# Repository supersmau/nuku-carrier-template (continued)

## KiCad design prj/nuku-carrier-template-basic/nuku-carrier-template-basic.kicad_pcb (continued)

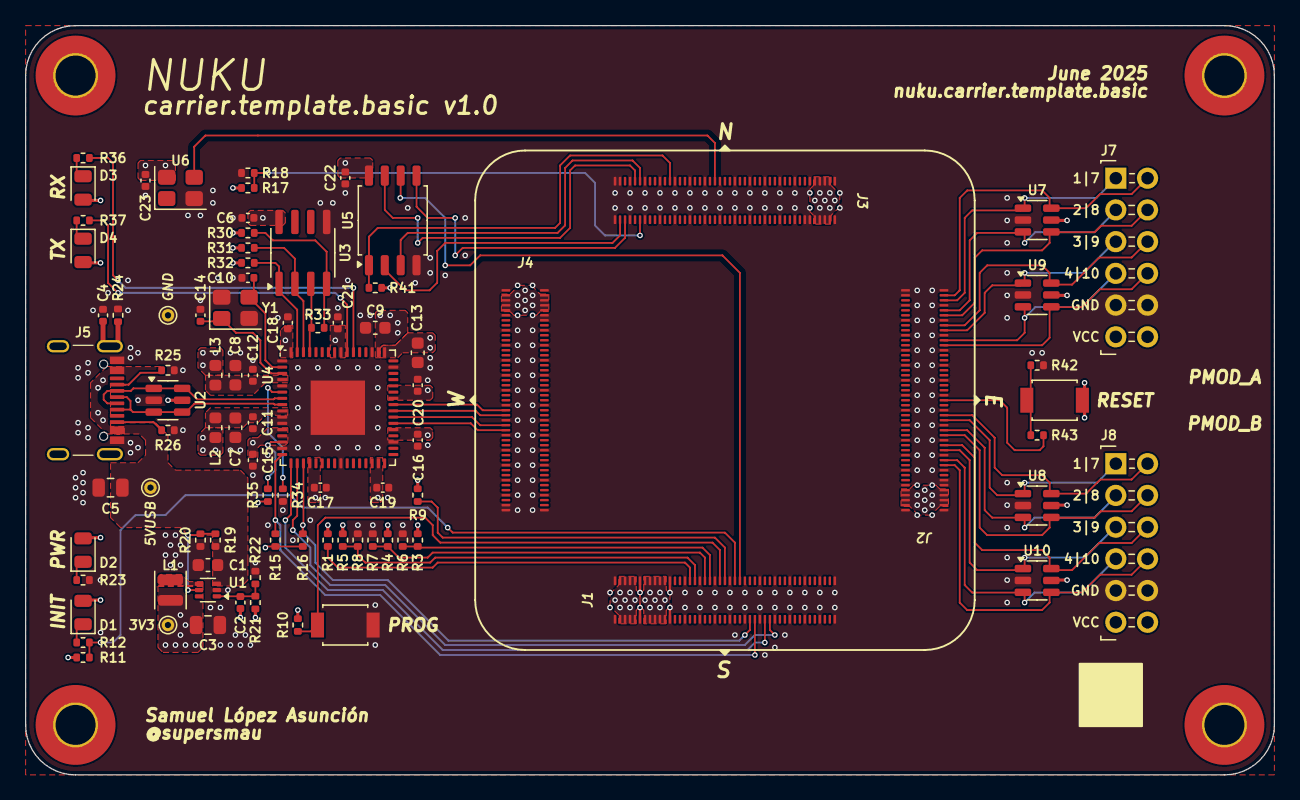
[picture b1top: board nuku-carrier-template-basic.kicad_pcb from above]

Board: 4 copper layers, 100.0 x 60.0 mm, 87 parts (0 on the bottom side), 69 nets.

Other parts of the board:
3V3, 5VUSB: TestPoint_THTPad_D1.0mm_Drill0.5mm
GND: TestPoint_THTPad_D1.0mm_Drill0.5mm

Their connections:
+3V3: 3V3.1; also elsewhere on the board
+5V: 5VUSB.1; also elsewhere on the board
GND: GND.1; also elsewhere on the board

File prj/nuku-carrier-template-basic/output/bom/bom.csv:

"Reference","Value","Footprint","Qty","DNP","LCSC"
"C1,C7,C8,C9,C13","4u7","Capacitor_SMD:C_0603_1608Metric","5","","C19666"
"C2,C10,C14","33p","Capacitor_SMD:C_0402_1005Metric","3","","C1562"
"C3,C5","47u","Capacitor_SMD:C_0805_2012Metric","2","","C16780"
"C4,C6,C11,C12,C15,C16,C17,C18,C19,C20,C21,C22,C23","470n","Capacitor_SMD:C_0402_1005Metric","13","","C47339"
"D1,D2,D3,D4","INIT,PWR,RX,TX","LED_SMD:LED_0805_2012Metric","4","","C2297"
"J1,J2,J3,J4","DF40HC(4.0)-90DS-0.4V","nuku:DF40HC(4.0)-90DS-0.4V","4","","C597947"
"J5","USB_C_Receptacle_USB2.0_16P","nuku:TYPE-C16PIN","1","","C393939"
"J7,J8","PMOD_A,PMOD_B","nuku:PMOD_PinSocket_2x06_P2.54mm_Horizontal","2","","C2936003"
"L1","1u","Inductor_SMD:L_Changjiang_FNR252010S","1","","C5832356"
"L2,L3","600","Inductor_SMD:L_0603_1608Metric","2","","C1002"
"R1,R38","0","Resistor_SMD:R_0402_1005Metric","2","","C17168"
"R5,R6,R7,R12,R17,R23,R35,R36,R37","1k","Resistor_SMD:R_0402_1005Metric","9","","C11702"
"R9","330","Resistor_SMD:R_0402_1005Metric","1","","C25104"
"R10,R11,R41,R42,R43","4k7","Resistor_SMD:R_0402_1005Metric","5","","C25900"
"R15,R16,R30,R31,R32","10k","Resistor_SMD:R_0402_1005Metric","5","","C25744"
"R19,R21","100k","Resistor_SMD:R_0402_1005Metric","2","","C25741"
"R20","200k","Resistor_SMD:R_0402_1005Metric","1","","C25764"
"R22","22k","Resistor_SMD:R_0402_1005Metric","1","","C25768"
"R24","1M","Resistor_SMD:R_0402_1005Metric","1","","C26083"
"R25,R26","5k1","Resistor_SMD:R_0402_1005Metric","2","","C25905"
"R33","2k2","Resistor_SMD:R_0402_1005Metric","1","","C25879"
"R34","12k","Resistor_SMD:R_0402_1005Metric","1","","C25752"
"SW1,SW2","PROG,RESET","nuku:TS-1088-AR02016","2","","C720477"
"U1","AP61302","Package_TO_SOT_SMD:SOT-563","1","","C3193204"
"U2,U7,U8,U9,U10","SRV05-4","Package_TO_SOT_SMD:SOT-23-6","5","","C7420376"
"U3","M93C56-WDW6TP","Package_SO:TSSOP-8_4.4x3mm_P0.65mm","1","","C2061074"
"U4","FT2232HQ","Package_DFN_QFN:QFN-64-1EP_9x9mm_P0.5mm_EP4.35x4.35mm","1","","C193662"
"U5","IS25LP064A","Package_SO:SOIC-8_5.3x5.3mm_P1.27mm","1","","C2841348"
"U6","OT3225100MJBA4SL","Crystal:Crystal_SMD_3225-4Pin_3.2x2.5mm","1","","C4353707"
"Y1","12 MHz","Crystal:Crystal_SMD_3225-4Pin_3.2x2.5mm","1","","C9002"

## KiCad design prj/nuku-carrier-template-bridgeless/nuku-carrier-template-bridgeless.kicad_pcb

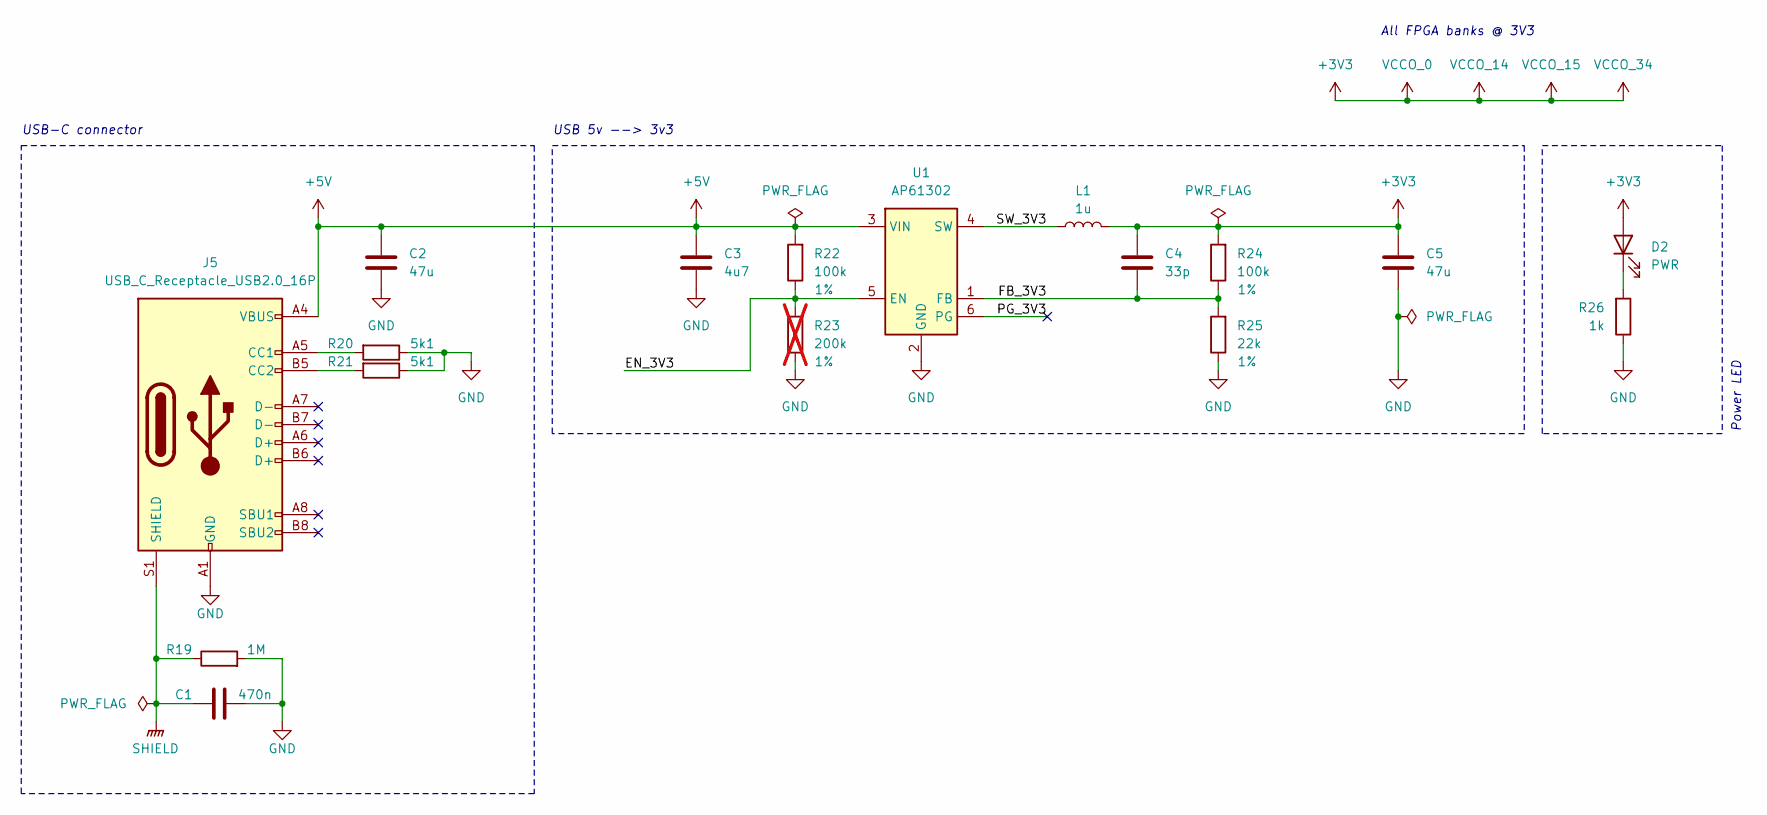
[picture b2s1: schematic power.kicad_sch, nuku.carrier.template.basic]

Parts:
C1: 470n; C_0402_1005Metric; LCSC C47339
C2, C5: 47u; C_0805_2012Metric; LCSC C16780
C3: 4u7; C_0603_1608Metric; LCSC C19666
C4: 33p; C_0402_1005Metric; LCSC C1562
D2: PWR; LED_0805_2012Metric; LCSC C2297
J5: USB_C_Receptacle_USB2.0_16P; TYPE-C16PIN; LCSC C393939
L1: 1u; L_Changjiang_FNR252010S; Mfr. Part FTC252010S1R0MBCA; LCSC C5832356
R19: 1M; R_0402_1005Metric; LCSC C26083
R20, R21: 5k1; R_0402_1005Metric; LCSC C25905
R22, R24: 100k; R_0402_1005Metric; Tolerance 1%; LCSC C25741
R23: 200k; R_0402_1005Metric; Tolerance 1%; LCSC C25764; not fitted
R25: 22k; R_0402_1005Metric; Tolerance 1%; LCSC C25768
R26: 1k; R_0402_1005Metric; LCSC C11702
U1: AP61302; SOT-563; LCSC C3193204

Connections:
+3V3: C4.1, C5.1, D2.2 (A), L1.2, R24.2; also elsewhere on the board
+5V: C2.1, C3.1, J5.A4 (VBUS), J5.A9 (VBUS), J5.B4 (VBUS), J5.B9 (VBUS), R22.2, U1.3 (VIN); also elsewhere on the board
/power/EN_3V3: R22.1, R23.2, U1.5 (EN)
/power/FB_3V3: C4.2, R24.1, R25.2, U1.1 (FB)
/power/PG_3V3: U1.6 (PG)
/power/SW_3V3: L1.1, U1.4 (SW)
GND: C1.1, C2.2, C3.2, C5.2, J5.A1 (GND), J5.A12 (GND), J5.B1 (GND), J5.B12 (GND), R19.2, R20.1, R21.1, R23.1, R25.1, R26.1, U1.2 (GND); also elsewhere on the board
unnamed: D2.1 (K), R26.2
unnamed: J5.A5 (CC1), R20.2
unnamed: J5.B5 (CC2), R21.2
SHIELD: C1.2, J5.S1 (SHIELD), R19.1

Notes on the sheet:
USB-C connector
All FPGA banks @ 3V3
USB 5v --> 3v3
Power LED

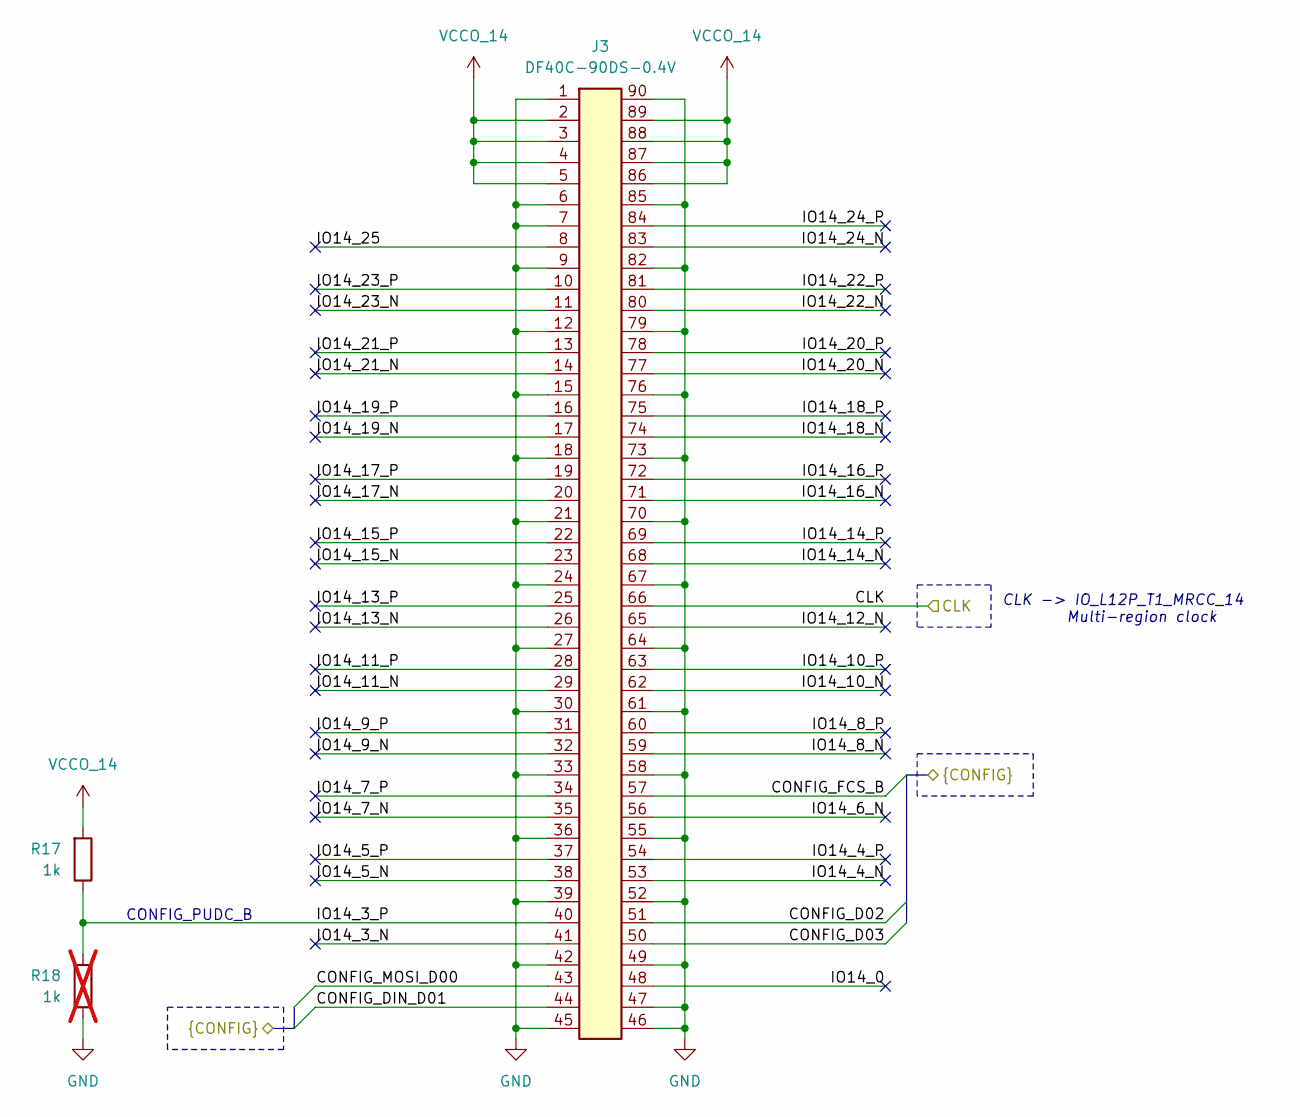
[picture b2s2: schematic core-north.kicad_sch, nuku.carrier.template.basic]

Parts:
J3: DF40C-90DS-0.4V; LCSC C2911197
R17: 1k; R_0402_1005Metric; LCSC C11702
R18: 1k; R_0402_1005Metric; LCSC C11702; not fitted

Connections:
+3V3: J3.2, J3.3, J3.4, J3.5, J3.86, J3.87, J3.88, J3.89, R17.2; also elsewhere on the board
/config/CLK: J3.66; also elsewhere on the board
/config/CONFIG_D02: J3.51; also elsewhere on the board
/config/CONFIG_D03: J3.50; also elsewhere on the board
/config/CONFIG_DIN_D01: J3.44; also elsewhere on the board
/config/CONFIG_FCS_B: J3.57; also elsewhere on the board
/config/CONFIG_MOSI_D00: J3.43; also elsewhere on the board
/core-north-14/IO14_0: J3.48
/core-north-14/IO14_3_N: J3.41
/core-north-14/IO14_3_P: J3.40, R17.1, R18.2
/core-north-14/IO14_4_N: J3.53
/core-north-14/IO14_4_P: J3.54
/core-north-14/IO14_5_N: J3.38
/core-north-14/IO14_5_P: J3.37
/core-north-14/IO14_6_N: J3.56
/core-north-14/IO14_7_N: J3.35
/core-north-14/IO14_7_P: J3.34
/core-north-14/IO14_8_N: J3.59
/core-north-14/IO14_8_P: J3.60
/core-north-14/IO14_9_N: J3.32
/core-north-14/IO14_9_P: J3.31
/core-north-14/IO14_10_N: J3.62
/core-north-14/IO14_10_P: J3.63
/core-north-14/IO14_11_N: J3.29
/core-north-14/IO14_11_P: J3.28
/core-north-14/IO14_12_N: J3.65
/core-north-14/IO14_13_N: J3.26
/core-north-14/IO14_13_P: J3.25
/core-north-14/IO14_14_N: J3.68
/core-north-14/IO14_14_P: J3.69
/core-north-14/IO14_15_N: J3.23
/core-north-14/IO14_15_P: J3.22
/core-north-14/IO14_16_N: J3.71
/core-north-14/IO14_16_P: J3.72
/core-north-14/IO14_17_N: J3.20
/core-north-14/IO14_17_P: J3.19
/core-north-14/IO14_18_N: J3.74
/core-north-14/IO14_18_P: J3.75
/core-north-14/IO14_19_N: J3.17
/core-north-14/IO14_19_P: J3.16
/core-north-14/IO14_20_N: J3.77
/core-north-14/IO14_20_P: J3.78
/core-north-14/IO14_21_N: J3.14
/core-north-14/IO14_21_P: J3.13
/core-north-14/IO14_22_N: J3.80
/core-north-14/IO14_22_P: J3.81
/core-north-14/IO14_23_N: J3.11
/core-north-14/IO14_23_P: J3.10
/core-north-14/IO14_24_N: J3.83
/core-north-14/IO14_24_P: J3.84
/core-north-14/IO14_25: J3.8
GND: J3.1, J3.6, J3.7, J3.9, J3.12, J3.15, J3.18, J3.21, J3.24, J3.27, J3.30, J3.33, J3.36, J3.39, J3.42, J3.45, J3.46, J3.47, J3.49, J3.52, J3.55, J3.58, J3.61, J3.64, J3.67, J3.70, J3.73, J3.76, J3.79, J3.82, J3.85, J3.90, R18.1; also elsewhere on the board

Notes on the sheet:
CONFIG_PUDC_B
CLK -> IO_L12P_T1_MRCC_14 Multi-region clock

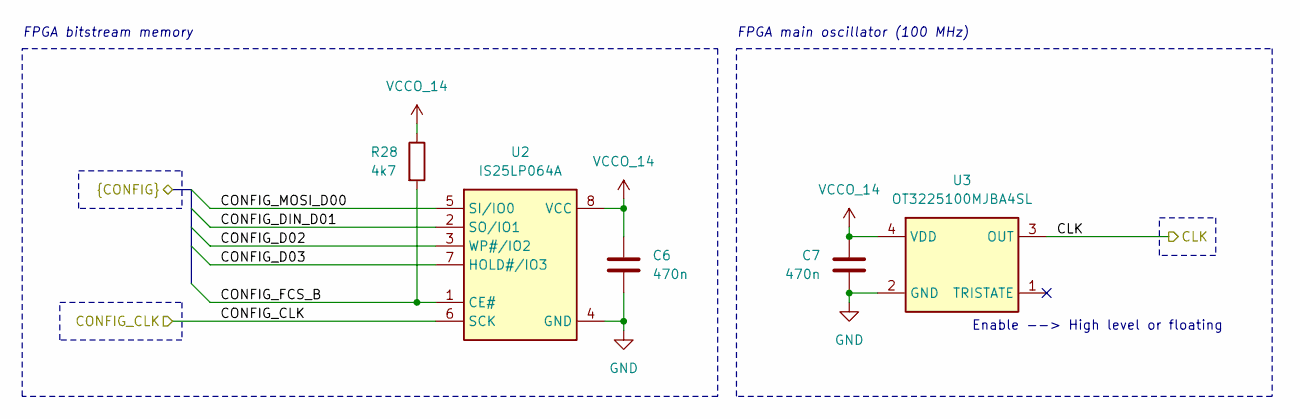
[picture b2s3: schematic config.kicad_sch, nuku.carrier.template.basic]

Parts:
C6, C7: 470n; C_0402_1005Metric; LCSC C47339
R28: 4k7; R_0402_1005Metric; LCSC C25900
U2: IS25LP064A; SOIC-8_5.3x5.3mm_P1.27mm; LCSC C2841348
U3: OT3225100MJBA4SL; Crystal_SMD_3225-4Pin_3.2x2.5mm; LCSC C4353707

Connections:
+3V3: C6.1, C7.1, R28.1, U2.8 (VCC), U3.4 (VDD); also elsewhere on the board
/config/CLK: U3.3 (OUT); also elsewhere on the board
/config/CONFIG_CLK: U2.6 (SCK); also elsewhere on the board
/config/CONFIG_D02: U2.3 (WP#/IO2); also elsewhere on the board
/config/CONFIG_D03: U2.7 (HOLD#/IO3); also elsewhere on the board
/config/CONFIG_DIN_D01: U2.2 (SO/IO1); also elsewhere on the board
/config/CONFIG_FCS_B: R28.2, U2.1 (CE#); also elsewhere on the board
/config/CONFIG_MOSI_D00: U2.5 (SI/IO0); also elsewhere on the board
GND: C6.2, C7.2, U2.4 (GND), U3.2 (GND); also elsewhere on the board

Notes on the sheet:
Enable --> High level or floating
FPGA main oscillator (100 MHz)
FPGA bitstream memory

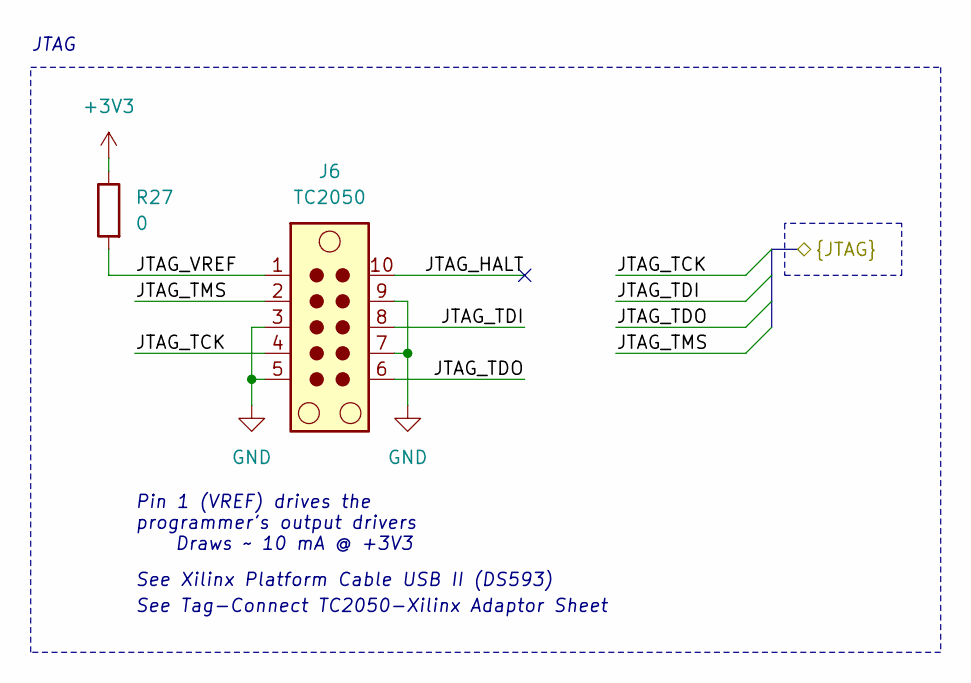
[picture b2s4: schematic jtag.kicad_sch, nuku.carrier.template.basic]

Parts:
J6: TC2050; Tag-Connect_TC2050-IDC-FP_2x05_P1.27mm_Vertical
R27: 0; R_0402_1005Metric; LCSC C17168

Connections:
+3V3: R27.1; also elsewhere on the board
/core-south-0/JTAG_TCK: J6.4; also elsewhere on the board
/core-south-0/JTAG_TDI: J6.8; also elsewhere on the board
/core-south-0/JTAG_TDO: J6.6; also elsewhere on the board
/core-south-0/JTAG_TMS: J6.2; also elsewhere on the board
/jtag/JTAG_HALT: J6.10
/jtag/JTAG_VREF: J6.1, R27.2
GND: J6.3, J6.5, J6.7, J6.9; also elsewhere on the board

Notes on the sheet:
Pin 1 (VREF) drives the programmer's output drivers Draws ~ 10 mA @ +3V3
See Tag-Connect TC2050-Xilinx Adaptor Sheet
See Xilinx Platform Cable USB II (DS593)
JTAG

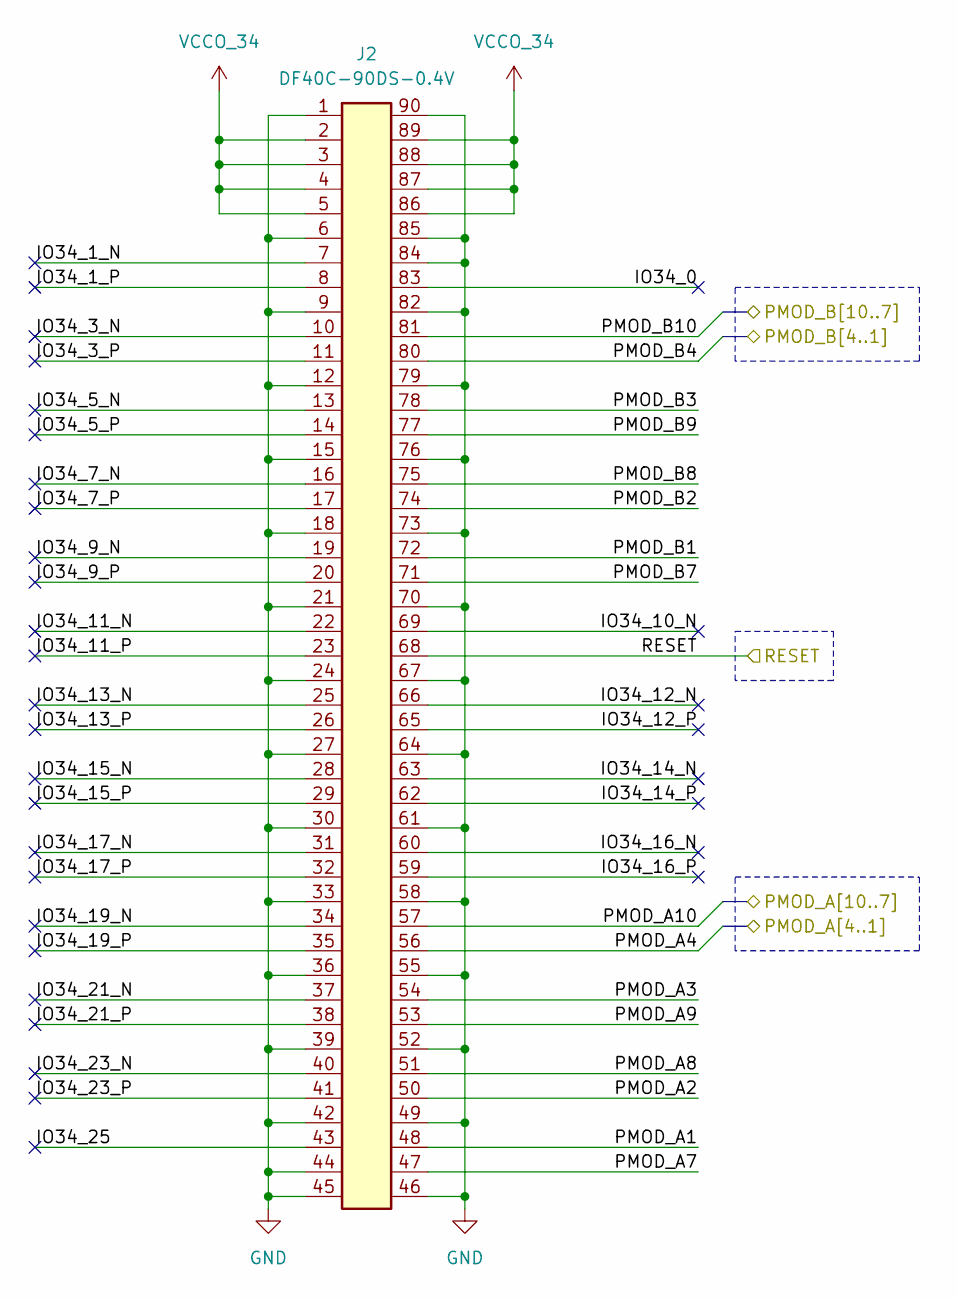
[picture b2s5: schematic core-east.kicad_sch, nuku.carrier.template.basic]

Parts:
J2: DF40C-90DS-0.4V; LCSC C2911197

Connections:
+3V3: J2.2, J2.3, J2.4, J2.5, J2.86, J2.87, J2.88, J2.89; also elsewhere on the board
/core-east-34/IO34_0: J2.83
/core-east-34/IO34_1_N: J2.7
/core-east-34/IO34_1_P: J2.8
/core-east-34/IO34_3_N: J2.10
/core-east-34/IO34_3_P: J2.11
/core-east-34/IO34_5_N: J2.13
/core-east-34/IO34_5_P: J2.14
/core-east-34/IO34_7_N: J2.16
/core-east-34/IO34_7_P: J2.17
/core-east-34/IO34_9_N: J2.19
/core-east-34/IO34_9_P: J2.20
/core-east-34/IO34_10_N: J2.69
/core-east-34/IO34_11_N: J2.22
/core-east-34/IO34_11_P: J2.23
/core-east-34/IO34_12_N: J2.66
/core-east-34/IO34_12_P: J2.65
/core-east-34/IO34_13_N: J2.25
/core-east-34/IO34_13_P: J2.26
/core-east-34/IO34_14_N: J2.63
/core-east-34/IO34_14_P: J2.62
/core-east-34/IO34_15_N: J2.28
/core-east-34/IO34_15_P: J2.29
/core-east-34/IO34_16_N: J2.60
/core-east-34/IO34_16_P: J2.59
/core-east-34/IO34_17_N: J2.31
/core-east-34/IO34_17_P: J2.32
/core-east-34/IO34_19_N: J2.34
/core-east-34/IO34_19_P: J2.35
/core-east-34/IO34_21_N: J2.37
/core-east-34/IO34_21_P: J2.38
/core-east-34/IO34_23_N: J2.40
/core-east-34/IO34_23_P: J2.41
/core-east-34/IO34_25: J2.43
/core-east-34/PMOD_A1: J2.48; also elsewhere on the board
/core-east-34/PMOD_A2: J2.50; also elsewhere on the board
/core-east-34/PMOD_A3: J2.54; also elsewhere on the board
/core-east-34/PMOD_A4: J2.56; also elsewhere on the board
/core-east-34/PMOD_A7: J2.47; also elsewhere on the board
/core-east-34/PMOD_A8: J2.51; also elsewhere on the board
/core-east-34/PMOD_A9: J2.53; also elsewhere on the board
/core-east-34/PMOD_A10: J2.57; also elsewhere on the board
/core-east-34/PMOD_B1: J2.72; also elsewhere on the board
/core-east-34/PMOD_B2: J2.74; also elsewhere on the board
/core-east-34/PMOD_B3: J2.78; also elsewhere on the board
/core-east-34/PMOD_B4: J2.80; also elsewhere on the board
/core-east-34/PMOD_B7: J2.71; also elsewhere on the board
/core-east-34/PMOD_B8: J2.75; also elsewhere on the board
/core-east-34/PMOD_B9: J2.77; also elsewhere on the board
/core-east-34/PMOD_B10: J2.81; also elsewhere on the board
/core-east-34/RESET: J2.68; also elsewhere on the board
GND: J2.1, J2.6, J2.9, J2.12, J2.15, J2.18, J2.21, J2.24, J2.27, J2.30, J2.33, J2.36, J2.39, J2.42, J2.44, J2.45, J2.46, J2.49, J2.52, J2.55, J2.58, J2.61, J2.64, J2.67, J2.70, J2.73, J2.76, J2.79, J2.82, J2.84, J2.85, J2.90; also elsewhere on the board

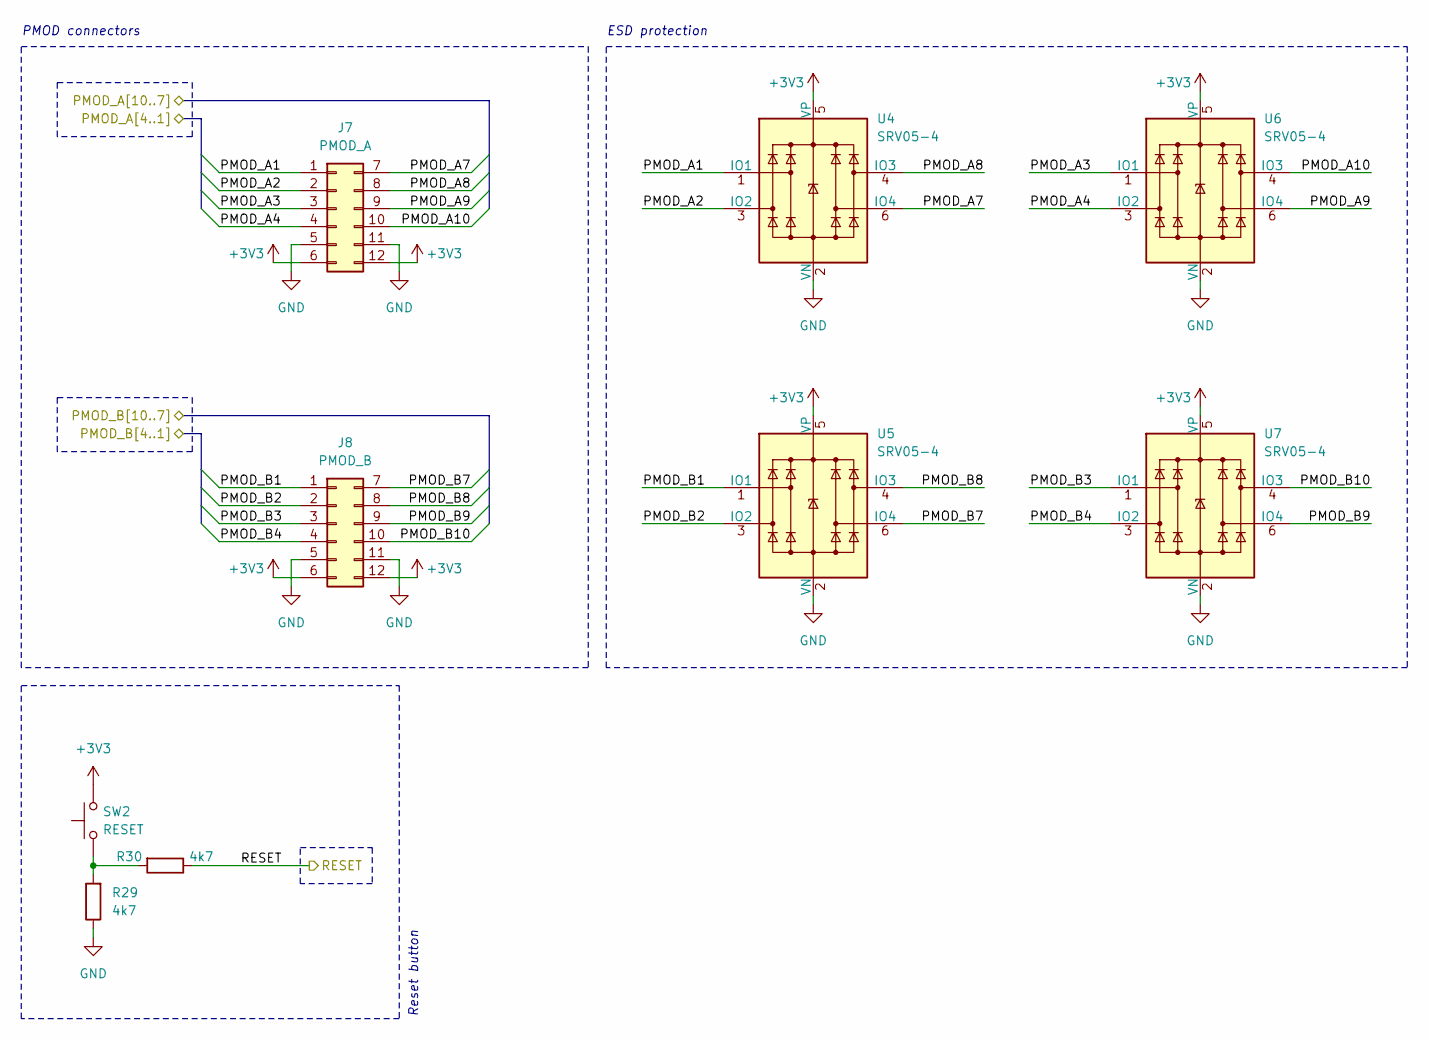
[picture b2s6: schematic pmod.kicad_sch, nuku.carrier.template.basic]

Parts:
J7: PMOD_A; PMOD_PinSocket_2x06_P2.54mm_Horizontal; LCSC C2936003
J8: PMOD_B; PMOD_PinSocket_2x06_P2.54mm_Horizontal; LCSC C2936003
R29, R30: 4k7; R_0402_1005Metric; LCSC C25900
SW2: RESET; TS-1088-AR02016; LCSC C720477
U4, U5, U6, U7: SRV05-4; SOT-23-6; LCSC C7420376

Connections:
+3V3: J7.6, J7.12, J8.6, J8.12, SW2.2, U4.5 (VP), U5.5 (VP), U6.5 (VP), U7.5 (VP); also elsewhere on the board
/core-east-34/PMOD_A1: J7.1, U4.1 (IO1); also elsewhere on the board
/core-east-34/PMOD_A2: J7.2, U4.3 (IO2); also elsewhere on the board
/core-east-34/PMOD_A3: J7.3, U6.1 (IO1); also elsewhere on the board
/core-east-34/PMOD_A4: J7.4, U6.3 (IO2); also elsewhere on the board
/core-east-34/PMOD_A7: J7.7, U4.6 (IO4); also elsewhere on the board
/core-east-34/PMOD_A8: J7.8, U4.4 (IO3); also elsewhere on the board
/core-east-34/PMOD_A9: J7.9, U6.6 (IO4); also elsewhere on the board
/core-east-34/PMOD_A10: J7.10, U6.4 (IO3); also elsewhere on the board
/core-east-34/PMOD_B1: J8.1, U5.1 (IO1); also elsewhere on the board
/core-east-34/PMOD_B2: J8.2, U5.3 (IO2); also elsewhere on the board
/core-east-34/PMOD_B3: J8.3, U7.1 (IO1); also elsewhere on the board
/core-east-34/PMOD_B4: J8.4, U7.3 (IO2); also elsewhere on the board
/core-east-34/PMOD_B7: J8.7, U5.6 (IO4); also elsewhere on the board
/core-east-34/PMOD_B8: J8.8, U5.4 (IO3); also elsewhere on the board
/core-east-34/PMOD_B9: J8.9, U7.6 (IO4); also elsewhere on the board
/core-east-34/PMOD_B10: J8.10, U7.4 (IO3); also elsewhere on the board
/core-east-34/RESET: R30.1; also elsewhere on the board
GND: J7.5, J7.11, J8.5, J8.11, R29.1, U4.2 (VN), U5.2 (VN), U6.2 (VN), U7.2 (VN); also elsewhere on the board
unnamed: R29.2, R30.2, SW2.1

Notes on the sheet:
ESD protection
Reset button
PMOD connectors

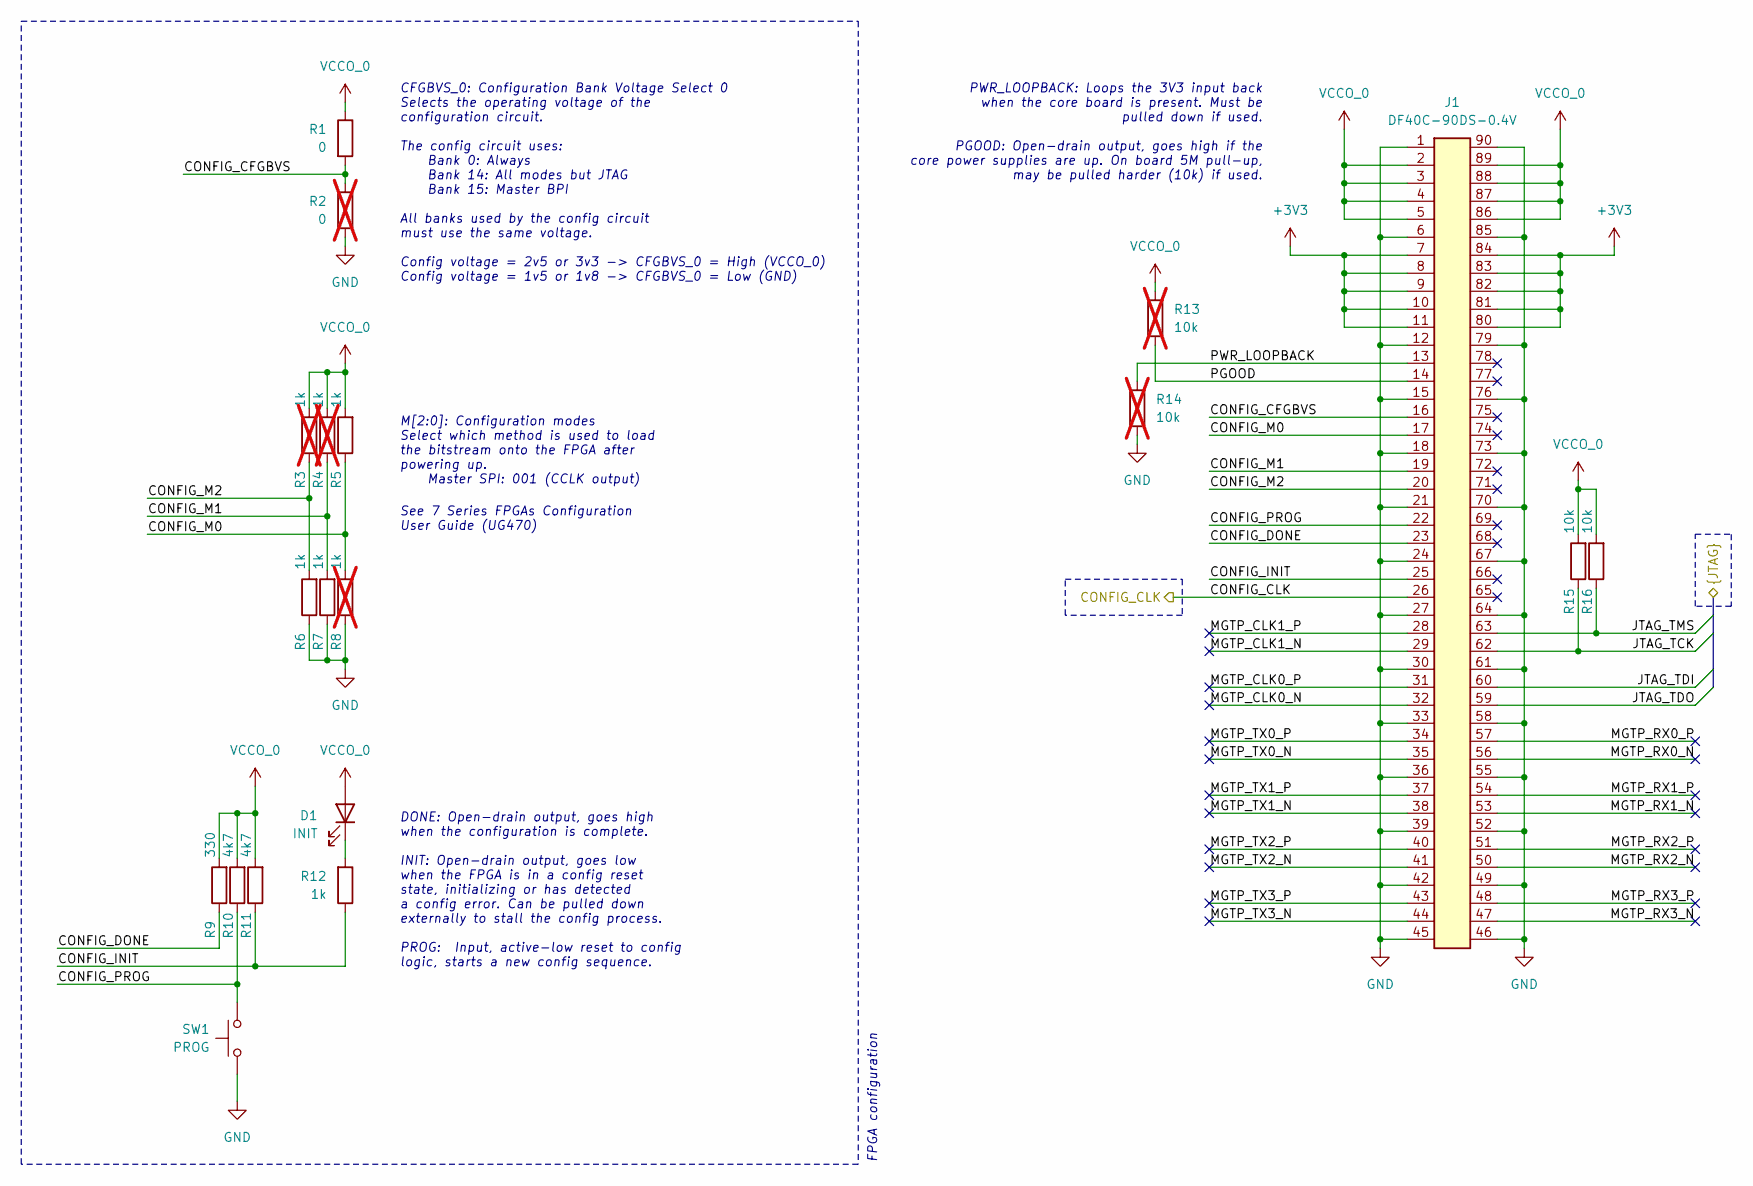
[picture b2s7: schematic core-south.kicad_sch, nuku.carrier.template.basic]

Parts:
D1: INIT; LED_0805_2012Metric; LCSC C2297
J1: DF40C-90DS-0.4V; LCSC C2911197
R1: 0; R_0402_1005Metric; LCSC C17168
R2: 0; R_0402_1005Metric; LCSC C17168; not fitted
R3, R4, R8: 1k; R_0402_1005Metric; LCSC C11702; not fitted
R5, R6, R7, R12: 1k; R_0402_1005Metric; LCSC C11702
R9: 330; R_0402_1005Metric; LCSC C25104
R10, R11: 4k7; R_0402_1005Metric; LCSC C25900
R13, R14: 10k; R_0402_1005Metric; LCSC C25744; not fitted
R15, R16: 10k; R_0402_1005Metric; LCSC C25744
SW1: PROG; TS-1088-AR02016; LCSC C720477

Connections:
+3V3: D1.2 (A), J1.2, J1.3, J1.4, J1.5, J1.7, J1.8, J1.9, J1.10, J1.11, J1.80, J1.81, J1.82, J1.83, J1.84, J1.86, J1.87, J1.88, J1.89, R1.1, R3.2, R4.2, R5.2, R9.2, R10.2, R11.2, R13.2, R15.2, R16.2; also elsewhere on the board
/config/CONFIG_CLK: J1.26; also elsewhere on the board
/core-south-0/CONFIG_CFGBVS: J1.16, R1.2, R2.1
/core-south-0/CONFIG_DONE: J1.23, R9.1
/core-south-0/CONFIG_INIT: J1.25, R11.1, R12.1
/core-south-0/CONFIG_M0: J1.17, R5.1, R8.2
/core-south-0/CONFIG_M1: J1.19, R4.1, R7.2
/core-south-0/CONFIG_M2: J1.20, R3.1, R6.2
/core-south-0/CONFIG_PROG: J1.22, R10.1, SW1.2
/core-south-0/JTAG_TCK: J1.62, R15.1; also elsewhere on the board
/core-south-0/JTAG_TDI: J1.60; also elsewhere on the board
/core-south-0/JTAG_TDO: J1.59; also elsewhere on the board
/core-south-0/JTAG_TMS: J1.63, R16.1; also elsewhere on the board
/core-south-0/MGTP_CLK0_N: J1.32
/core-south-0/MGTP_CLK0_P: J1.31
/core-south-0/MGTP_CLK1_N: J1.29
/core-south-0/MGTP_CLK1_P: J1.28
/core-south-0/MGTP_RX0_N: J1.56
/core-south-0/MGTP_RX0_P: J1.57
/core-south-0/MGTP_RX1_N: J1.53
/core-south-0/MGTP_RX1_P: J1.54
/core-south-0/MGTP_RX2_N: J1.50
/core-south-0/MGTP_RX2_P: J1.51
/core-south-0/MGTP_RX3_N: J1.47
/core-south-0/MGTP_RX3_P: J1.48
/core-south-0/MGTP_TX0_N: J1.35
/core-south-0/MGTP_TX0_P: J1.34
/core-south-0/MGTP_TX1_N: J1.38
/core-south-0/MGTP_TX1_P: J1.37
/core-south-0/MGTP_TX2_N: J1.41
/core-south-0/MGTP_TX2_P: J1.40
/core-south-0/MGTP_TX3_N: J1.44
/core-south-0/MGTP_TX3_P: J1.43
/core-south-0/PGOOD: J1.14, R13.1
/core-south-0/PWR_LOOPBACK: J1.13, R14.2
GND: J1.1, J1.6, J1.12, J1.15, J1.18, J1.21, J1.24, J1.27, J1.30, J1.33, J1.36, J1.39, J1.42, J1.45, J1.46, J1.49, J1.52, J1.55, J1.58, J1.61, J1.64, J1.67, J1.70, J1.73, J1.76, J1.79, J1.85, J1.90, R2.2, R6.1, R7.1, R8.1, R14.1, SW1.1; also elsewhere on the board
unnamed: D1.1 (K), R12.2

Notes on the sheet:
M[2:0]: Configuration modes Select which method is used to load the bitstream onto the FPGA after powering up. Master SPI: 001 (CCLK output)
FPGA configuration
See 7 Series FPGAs Configuration User Guide (UG470)
DONE: Open-drain output, goes high when the configuration is complete. INIT: Open-drain output, goes low when the FPGA is in a config reset state, initializing or has detected a config error. Can be pulled down externally to stall the config process. PROG: Input, active-low reset to config logic, s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
CFGBVS_0: Configuration Bank Voltage Select 0 Selects the operating voltage of the configuration circuit. The config circuit uses: Bank 0: Always Bank 14: All modes but JTAG Bank 15: Master BPI All banks used by the config circuit must use the same voltage. Config voltage = 2v5 or 3v3 -> CFGBVS_0 =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
PWR_LOOPBACK: Loops the 3V3 input back when the core board is present. Must be pulled down if used. PGOOD: Open-drain output, goes high if the core power supplies are up. On board 5M pull-up, may be pulled harder (10k) if used.

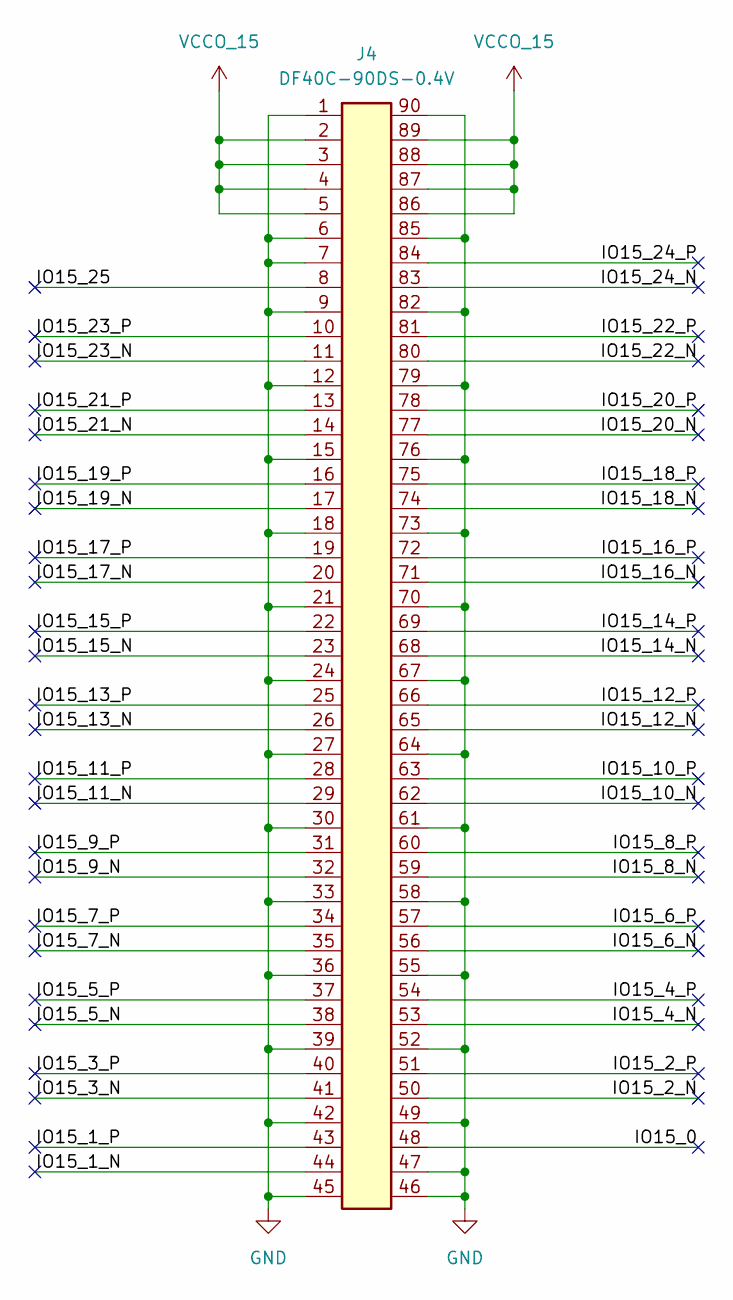
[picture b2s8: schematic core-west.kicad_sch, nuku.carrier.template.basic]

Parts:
J4: DF40C-90DS-0.4V; LCSC C2911197

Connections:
+3V3: J4.2, J4.3, J4.4, J4.5, J4.86, J4.87, J4.88, J4.89; also elsewhere on the board
/core-west-15/IO15_0: J4.48
/core-west-15/IO15_1_N: J4.44
/core-west-15/IO15_1_P: J4.43
/core-west-15/IO15_2_N: J4.50
/core-west-15/IO15_2_P: J4.51
/core-west-15/IO15_3_N: J4.41
/core-west-15/IO15_3_P: J4.40
/core-west-15/IO15_4_N: J4.53
/core-west-15/IO15_4_P: J4.54
/core-west-15/IO15_5_N: J4.38
/core-west-15/IO15_5_P: J4.37
/core-west-15/IO15_6_N: J4.56
/core-west-15/IO15_6_P: J4.57
/core-west-15/IO15_7_N: J4.35
/core-west-15/IO15_7_P: J4.34
/core-west-15/IO15_8_N: J4.59
/core-west-15/IO15_8_P: J4.60
/core-west-15/IO15_9_N: J4.32
/core-west-15/IO15_9_P: J4.31
/core-west-15/IO15_10_N: J4.62
/core-west-15/IO15_10_P: J4.63
/core-west-15/IO15_11_N: J4.29
/core-west-15/IO15_11_P: J4.28
/core-west-15/IO15_12_N: J4.65
/core-west-15/IO15_12_P: J4.66
/core-west-15/IO15_13_N: J4.26
/core-west-15/IO15_13_P: J4.25
/core-west-15/IO15_14_N: J4.68
/core-west-15/IO15_14_P: J4.69
/core-west-15/IO15_15_N: J4.23
/core-west-15/IO15_15_P: J4.22
/core-west-15/IO15_16_N: J4.71
/core-west-15/IO15_16_P: J4.72
/core-west-15/IO15_17_N: J4.20
/core-west-15/IO15_17_P: J4.19
/core-west-15/IO15_18_N: J4.74
/core-west-15/IO15_18_P: J4.75
/core-west-15/IO15_19_N: J4.17
/core-west-15/IO15_19_P: J4.16
/core-west-15/IO15_20_N: J4.77
/core-west-15/IO15_20_P: J4.78
/core-west-15/IO15_21_N: J4.14
/core-west-15/IO15_21_P: J4.13
/core-west-15/IO15_22_N: J4.80
/core-west-15/IO15_22_P: J4.81
/core-west-15/IO15_23_N: J4.11
/core-west-15/IO15_23_P: J4.10
/core-west-15/IO15_24_N: J4.83
/core-west-15/IO15_24_P: J4.84
/core-west-15/IO15_25: J4.8
GND: J4.1, J4.6, J4.7, J4.9, J4.12, J4.15, J4.18, J4.21, J4.24, J4.27, J4.30, J4.33, J4.36, J4.39, J4.42, J4.45, J4.46, J4.47, J4.49, J4.52, J4.55, J4.58, J4.61, J4.64, J4.67, J4.70, J4.73, J4.76, J4.79, J4.82, J4.85, J4.90; also elsewhere on the board

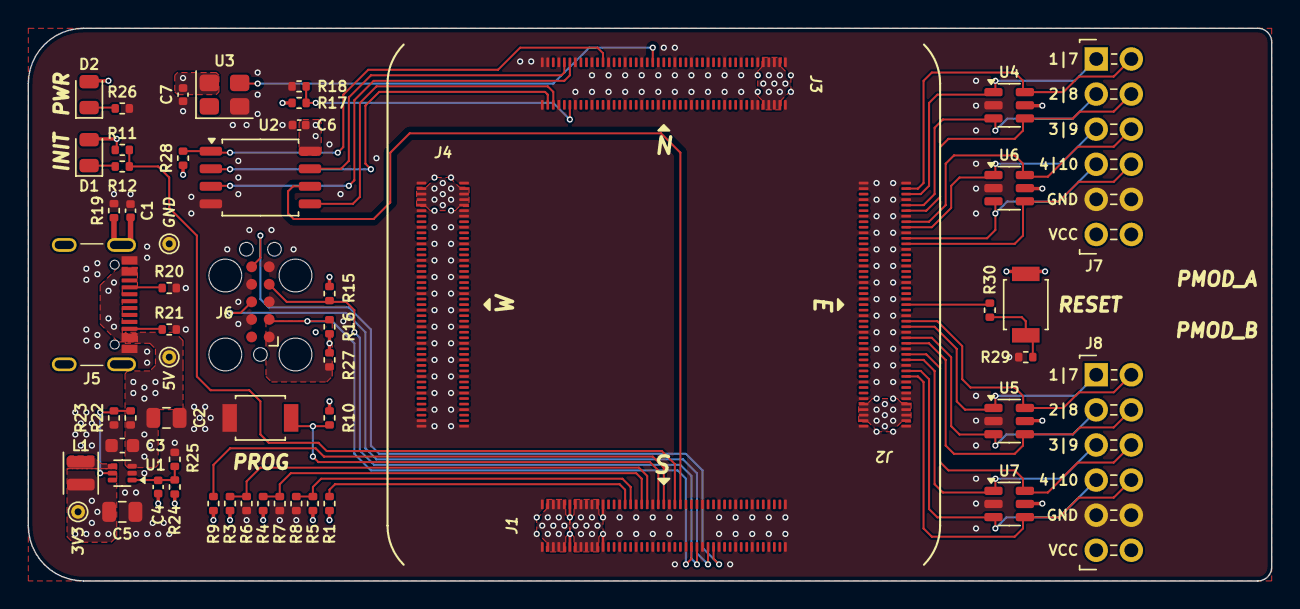
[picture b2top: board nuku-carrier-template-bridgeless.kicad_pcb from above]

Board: 4 copper layers, 90.0 x 40.0 mm, 57 parts (0 on the bottom side), 49 nets.

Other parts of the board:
3V3, 5V: TestPoint_THTPad_D1.0mm_Drill0.5mm
GND: TestPoint_THTPad_D1.0mm_Drill0.5mm

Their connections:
+3V3: 3V3.1; also elsewhere on the board
+5V: 5V.1; also elsewhere on the board
GND: GND.1; also elsewhere on the board
